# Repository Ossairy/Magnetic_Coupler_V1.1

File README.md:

# Magnetic_Coupler

Project Objective :  
   
    the project objective is to design and manufacture Motor testing setup.
    
Project Duration :
    
    August 2021 ; during my internship period in MRS research Lab -Multi Robot Systems- in german university in cairo.
    
Project Description :   
    First the system is designed and modeled on Solidworks and then the designed parts is manufactured using Laser cutting machine , conventional Lathe , conventional milling machine ,and CNC bending machine. It was desired to measure the torque of a motor that wanted to be tested however applying so much force on the motor shaft may hurt the motor ,so I choosed the magnetic coupler to be added to the system to add the following :
        - Mechanical fusing.
        - No load starting.
At the end the system succeded to acheive the desired objective to measure the motor torque , no load speed electrical power ,and efficiency.

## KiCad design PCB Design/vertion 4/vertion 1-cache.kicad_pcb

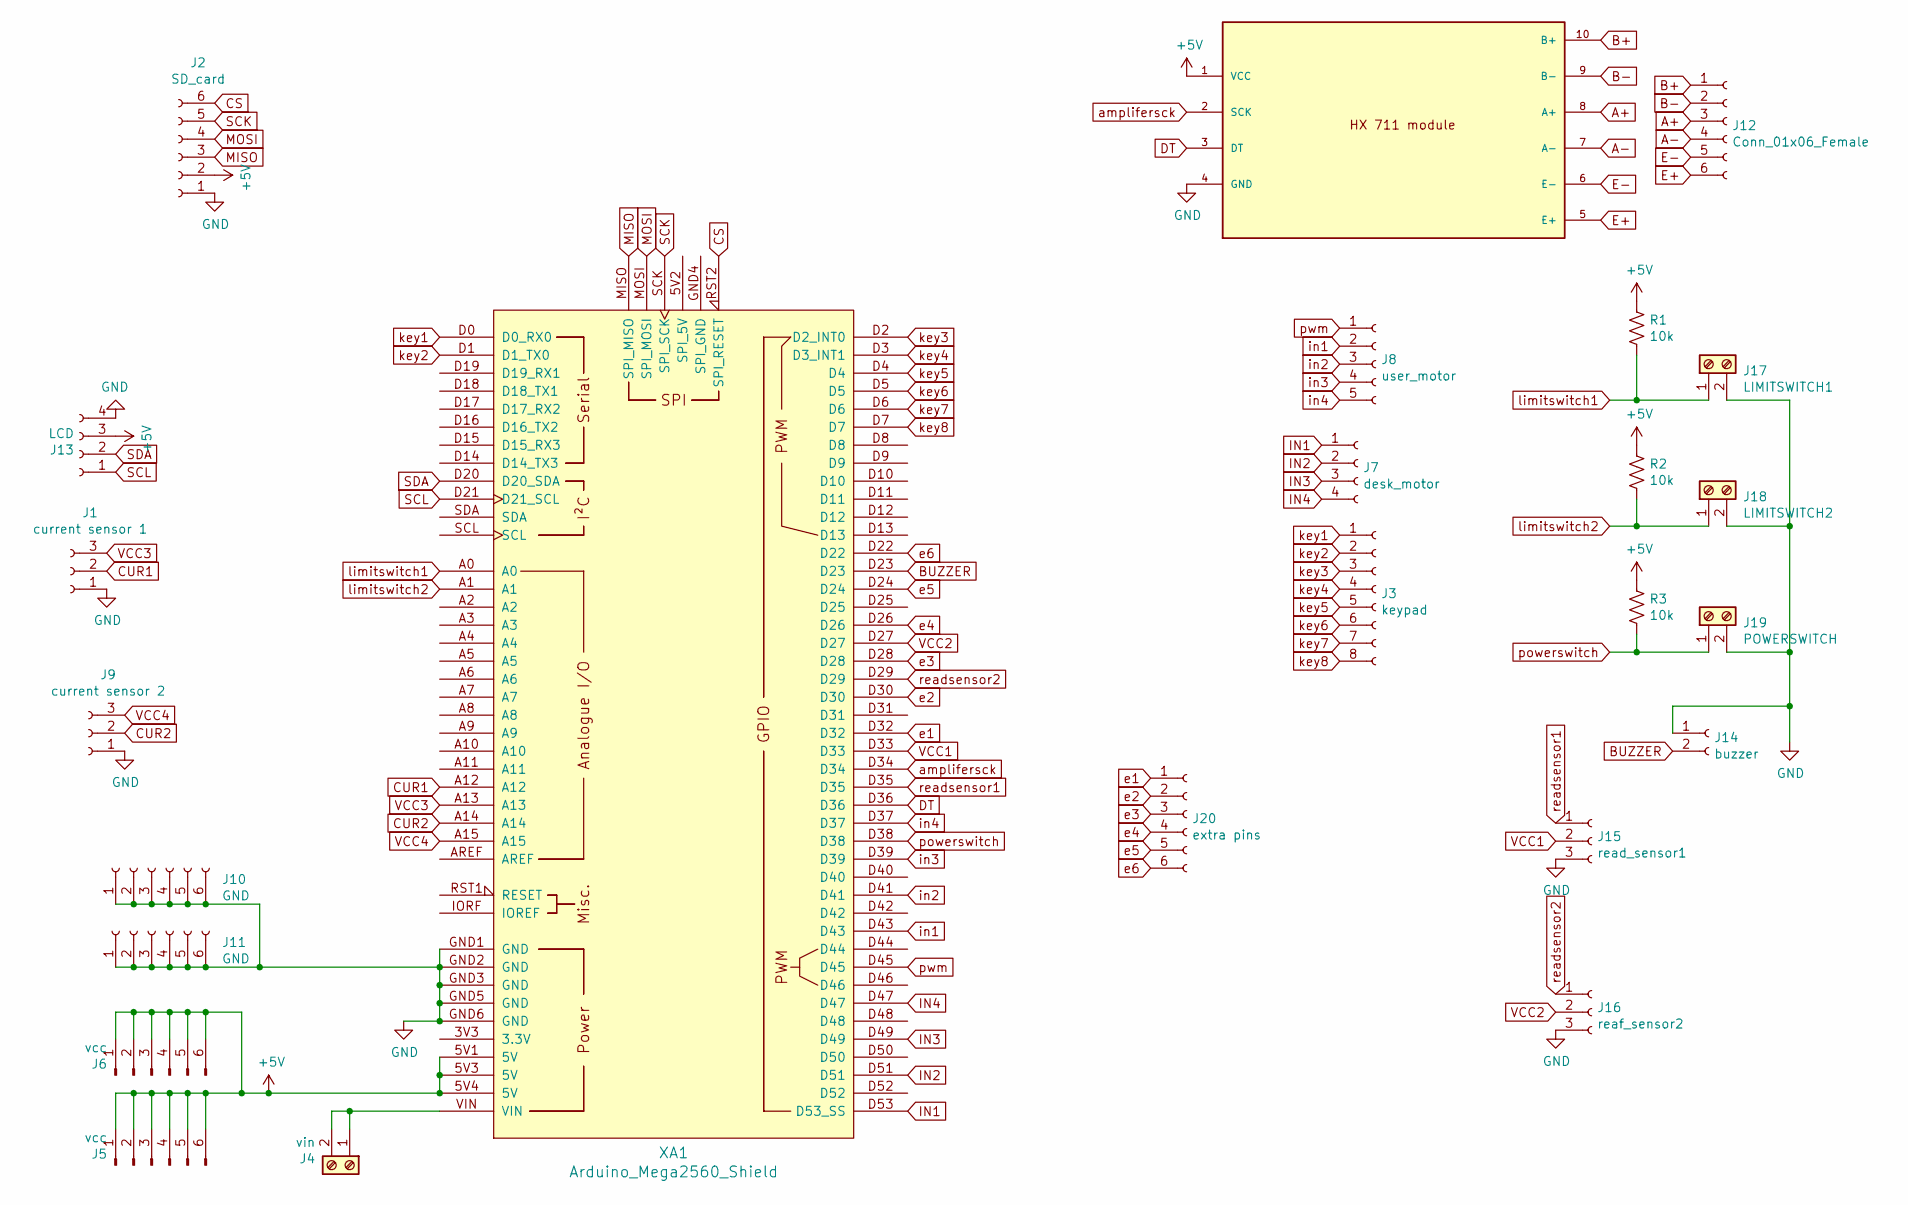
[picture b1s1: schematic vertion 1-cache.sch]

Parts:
HX7111: HX711
J1: current sensor 1; PinSocket_1x03_P2.54mm_Vertical
J2: SD_card; PinSocket_1x06_P2.54mm_Vertical
J3: keypad; PinSocket_1x08_P2.54mm_Vertical
J4: vin; TerminalBlock_Altech_AK300-2_P5.00mm
J5, J6: vcc; PinHeader_1x06_P2.54mm_Vertical
J7: desk_motor; PinSocket_1x04_P2.54mm_Vertical
J8: user_motor; PinSocket_1x05_P2.54mm_Vertical
J9: current sensor 2; PinSocket_1x03_P2.54mm_Vertical
J10, J11: GND; PinHeader_1x06_P2.54mm_Vertical
J12: Conn_01x06_Female; PinSocket_1x06_P2.54mm_Vertical
J13: LCD; PinSocket_1x04_P2.54mm_Vertical
J14: buzzer; PinSocket_1x02_P2.54mm_Vertical
J15: read_sensor1; PinSocket_1x03_P2.54mm_Vertical
J16: reaf_sensor2; PinSocket_1x03_P2.54mm_Vertical
J17: LIMITSWITCH1; TerminalBlock_Altech_AK300-2_P5.00mm
J18: LIMITSWITCH2; TerminalBlock_Altech_AK300-2_P5.00mm
J19: POWERSWITCH; TerminalBlock_Altech_AK300-2_P5.00mm
J20: extra pins; PinSocket_1x06_P2.54mm_Vertical
R1, R2, R3: 10k; R_Axial_DIN0204_L3.6mm_D1.6mm_P5.08mm_Horizontal
XA1: Arduino_Mega2560_Shield

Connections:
+5V: HX7111.1 (VCC), J2.2, J5.1, J5.2, J5.3, J5.4, J5.5, J5.6, J6.1, J6.2, J6.3, J6.4, J6.5, J6.6, J13.3, R1.1, R2.1, R3.1, XA1.5V1 (5V), XA1.5V3 (5V), XA1.5V4 (5V)
A+: HX7111.8 (A+), J12.3
A-: HX7111.7 (A-), J12.4
B+: HX7111.10 (B+), J12.1
B-: HX7111.9 (B-), J12.2
BUZZER: J14.2, XA1.D23
CS: J2.6, XA1.RST2 (SPI_RESET)
CUR1: J1.2, XA1.A12
CUR2: J9.2, XA1.A14
DT: HX7111.3 (DT), XA1.D36
E+: HX7111.5 (E+), J12.6
E-: HX7111.6 (E-), J12.5
GND: HX7111.4 (GND), J1.1, J2.1, J9.1, J10.1, J10.2, J10.3, J10.4, J10.5, J10.6, J11.1, J11.2, J11.3, J11.4, J11.5, J11.6, J13.4, J14.1, J15.3, J16.3, J17.2, J18.2, J19.2, XA1.GND1 (GND), XA1.GND2 (GND), XA1.GND3 (GND), XA1.GND5 (GND), XA1.GND6 (GND)
IN1: J7.1, XA1.D53 (D53_SS)
IN2: J7.2, XA1.D51
IN3: J7.3, XA1.D49
IN4: J7.4, XA1.D47
MISO: J2.3, XA1.MISO (SPI_MISO)
MOSI: J2.4, XA1.MOSI (SPI_MOSI)
unnamed: J4.1, J4.2, XA1.VIN
SCK: J2.5, XA1.SCK (SPI_SCK)
SCL: J13.1, XA1.D21 (D21_SCL)
SDA: J13.2, XA1.D20 (D20_SDA)
VCC1: J15.2, XA1.D33
VCC2: J16.2, XA1.D27
VCC3: J1.3, XA1.A13
VCC4: J9.3, XA1.A15
amplifersck: HX7111.2 (SCK), XA1.D34
e1: J20.1, XA1.D32
e2: J20.2, XA1.D30
e3: J20.3, XA1.D28
e4: J20.4, XA1.D26
e5: J20.5, XA1.D24
e6: J20.6, XA1.D22
in1: J8.2, XA1.D43
in2: J8.3, XA1.D41
in3: J8.4, XA1.D39
in4: J8.5, XA1.D37
key1: J3.1, XA1.D0 (D0_RX0)
key2: J3.2, XA1.D1 (D1_TX0)
key3: J3.3, XA1.D2 (D2_INT0)
key4: J3.4, XA1.D3 (D3_INT1)
key5: J3.5, XA1.D4
key6: J3.6, XA1.D5
key7: J3.7, XA1.D6
key8: J3.8, XA1.D7
limitswitch1: J17.1, R1.2, XA1.A0
limitswitch2: J18.1, R2.2, XA1.A1
powerswitch: J19.1, R3.2, XA1.D38
pwm: J8.1, XA1.D45
readsensor1: J15.1, XA1.D35
readsensor2: J16.1, XA1.D29

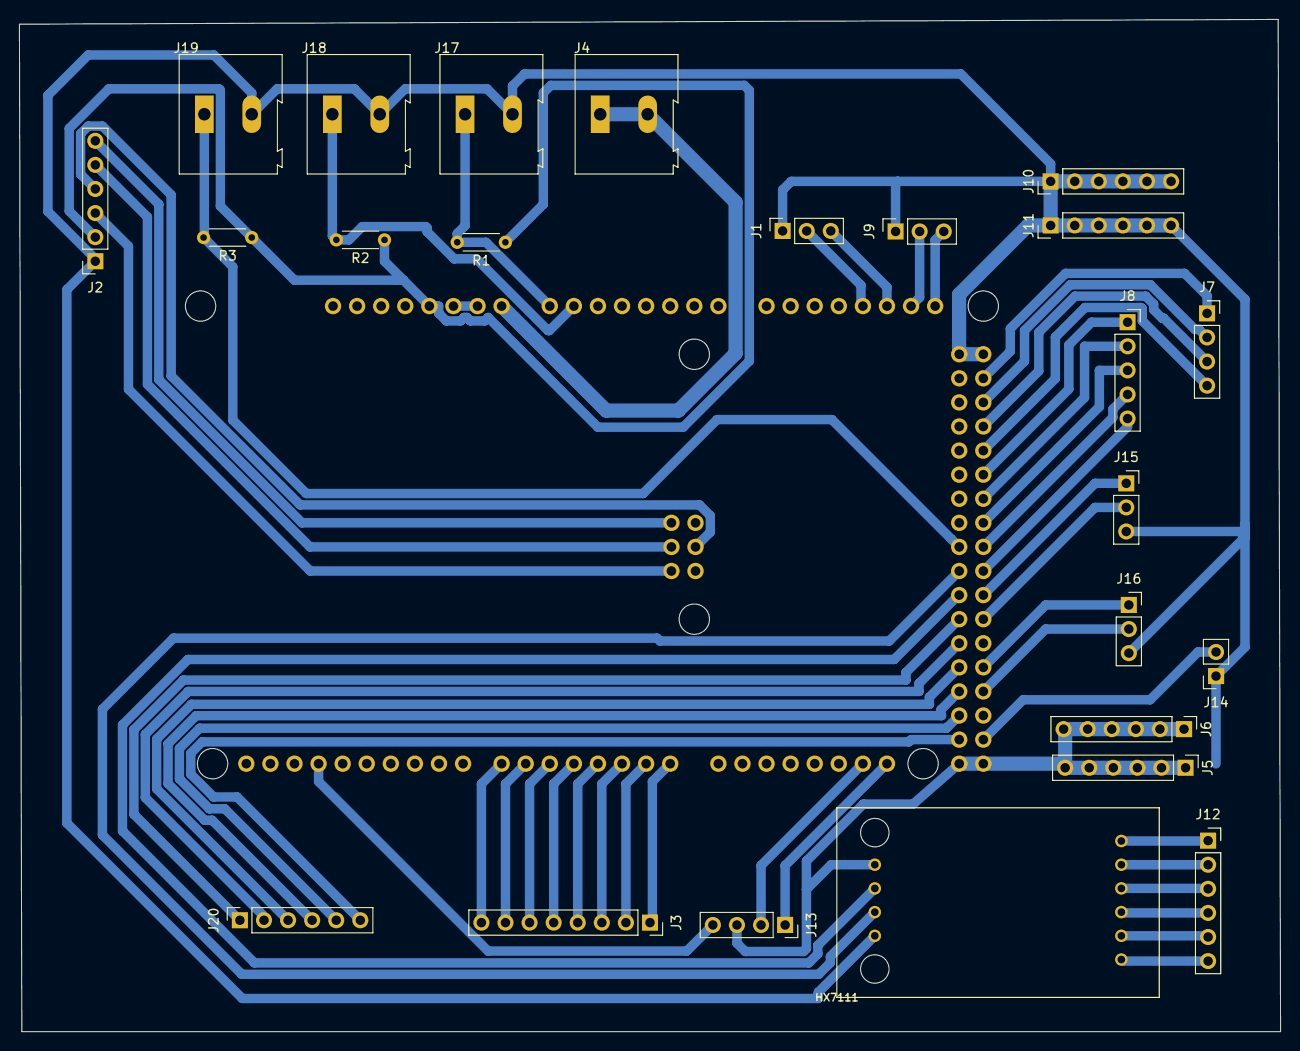
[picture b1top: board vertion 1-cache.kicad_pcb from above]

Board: 2 copper layers, 133.0 x 106.8 mm, 25 parts (1 on the bottom side), 52 nets.
